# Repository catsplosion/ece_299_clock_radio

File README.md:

Development repo for the ECE 299 clock-radio project.

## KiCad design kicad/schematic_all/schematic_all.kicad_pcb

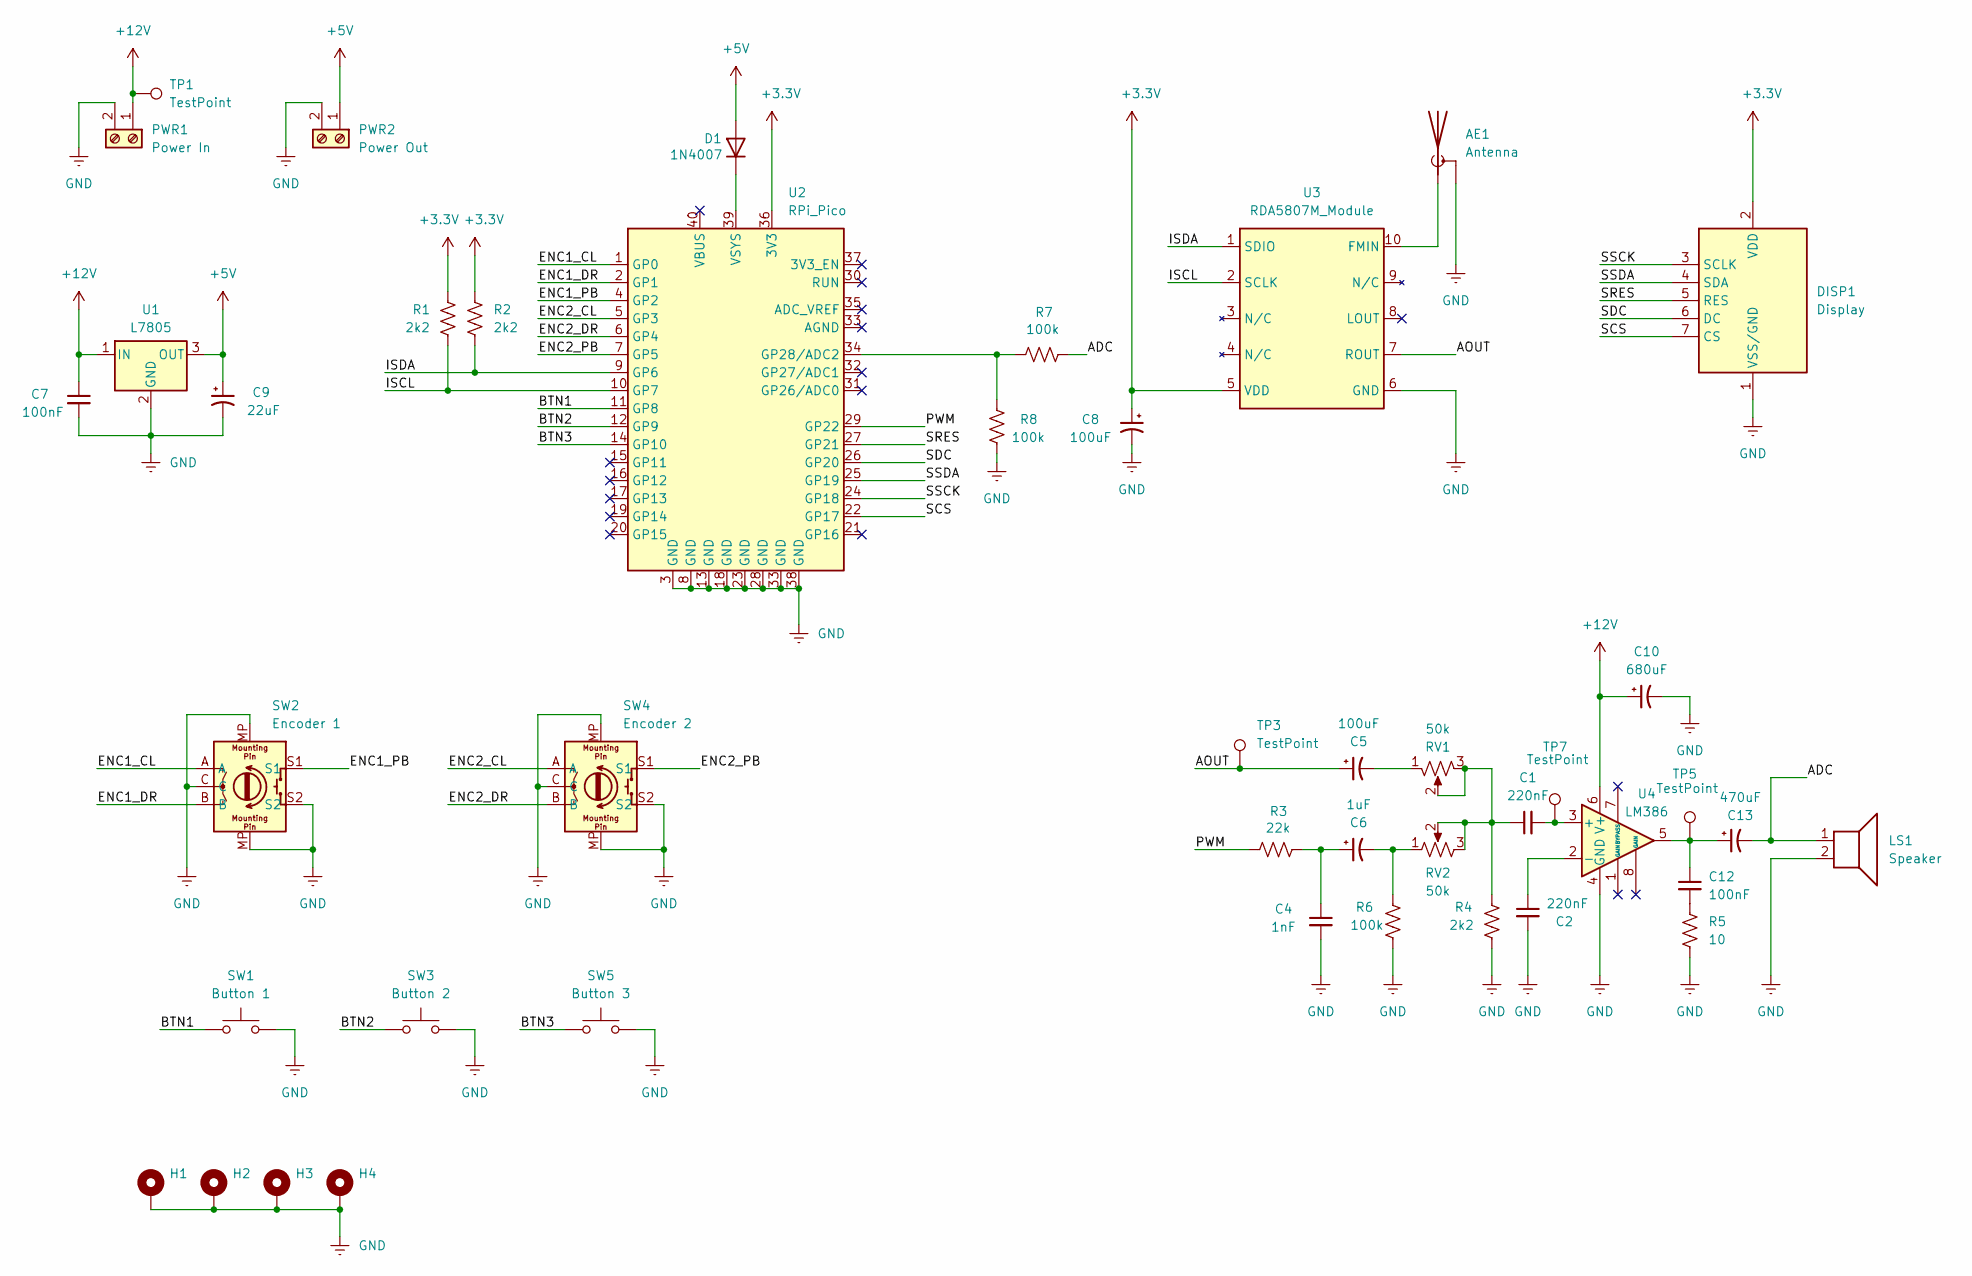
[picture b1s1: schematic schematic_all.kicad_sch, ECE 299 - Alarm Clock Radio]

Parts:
AE1: Antenna; TerminalBlock_Phoenix_MKDS-1,5-2_1x02_P5.00mm_Horizontal
C1, C2: 220nF; C_Disc_D5.0mm_W2.5mm_P5.00mm
C4: 1nF; C_Disc_D5.0mm_W2.5mm_P5.00mm
C5, C8: 100uF; CP_Radial_D5.0mm_P2.00mm
C6: 1uF; CP_Radial_D5.0mm_P2.00mm
C7, C12: 100nF; C_Disc_D3.0mm_W2.0mm_P2.50mm
C9: 22uF; CP_Radial_D5.0mm_P2.00mm
C10: 680uF; CP_Radial_D8.0mm_P3.50mm
C13: 470uF; CP_Radial_D8.0mm_P3.50mm
D1: 1N4007; D_DO-41_SOD81_P10.16mm_Horizontal
DISP1: Display; TerminalBlock_Phoenix_MKDS-1,5-7_1x07_P5.00mm_Horizontal
H1, H2, H3, H4: MountingHole_3.2mm_M3_Pad
LS1: Speaker; TerminalBlock_Phoenix_MKDS-1,5-2_1x02_P5.00mm_Horizontal
PWR1: Power In; TerminalBlock_Phoenix_MKDS-1,5-2_1x02_P5.00mm_Horizontal
PWR2: Power Out; PinHeader_1x02_P2.54mm_Vertical
R1, R2, R4: 2k2; R_Axial_DIN0207_L6.3mm_D2.5mm_P10.16mm_Horizontal
R3: 22k; R_Axial_DIN0207_L6.3mm_D2.5mm_P10.16mm_Horizontal
R5: 10; R_Axial_DIN0207_L6.3mm_D2.5mm_P10.16mm_Horizontal
R6, R7, R8: 100k; R_Axial_DIN0207_L6.3mm_D2.5mm_P10.16mm_Horizontal
RV1, RV2: 50k; Bourns_PTV09_Horiz
SW1: Button 1; TerminalBlock_Phoenix_MKDS-1,5-2_1x02_P5.00mm_Horizontal
SW2: Encoder 1; TerminalBlock_Phoenix_MKDS-1,5-4_1x04_P5.00mm_Horizontal
SW3: Button 2; TerminalBlock_Phoenix_MKDS-1,5-2_1x02_P5.00mm_Horizontal
SW4: Encoder 2; TerminalBlock_Phoenix_MKDS-1,5-4_1x04_P5.00mm_Horizontal
SW5: Button 3; TerminalBlock_Phoenix_MKDS-1,5-2_1x02_P5.00mm_Horizontal
TP1, TP3, TP5, TP7: TestPoint; PinHeader_1x01_P2.54mm_Vertical
U1: L7805; TO-220-3_Vertical
U2: RPi_Pico; RPi_Pico_TH
U3: RDA5807M_Module; RDA5807M_Module_TH
U4: LM386; DIP-8_W7.62mm_Socket

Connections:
+3.3V: C8.1, DISP1.2 (VDD), R1.1, R2.1, U2.36 (3V3), U3.5 (VDD)
+5V: C9.1, D1.2 (A), PWR2.1, U1.3 (OUT)
+12V: C7.1, C10.1, PWR1.1, TP1.1, U1.1 (IN), U4.6 (V+)
/ADC: C13.2, LS1.1, R7.2
/AOUT: C5.1, TP3.1, U3.7 (ROUT)
/BTN1: SW1.1, U2.11 (GP8)
/BTN2: SW3.1, U2.12 (GP9)
/BTN3: SW5.1, U2.14 (GP10)
/ENC1_CL: SW2.A, U2.1 (GP0)
/ENC1_DR: SW2.B, U2.2 (GP1)
/ENC1_PB: SW2.S1, U2.4 (GP2)
/ENC2_CL: SW4.A, U2.5 (GP3)
/ENC2_DR: SW4.B, U2.6 (GP4)
/ENC2_PB: SW4.S1, U2.7 (GP5)
/ISCL: R1.2, U2.10 (GP7), U3.2 (SCLK)
/ISDA: R2.2, U2.9 (GP6), U3.1 (SDIO)
/PWM: R3.2, U2.29 (GP22)
/SCS: DISP1.7 (CS), U2.22 (GP17)
/SDC: DISP1.6 (DC), U2.26 (GP20)
/SRES: DISP1.5 (RES), U2.27 (GP21)
/SSCK: DISP1.3 (SCLK), U2.24 (GP18)
/SSDA: DISP1.4 (SDA), U2.25 (GP19)
GND: AE1.2 (Shield), C2.2, C4.2, C7.2, C8.2, C9.2, C10.2, DISP1.1 (VSS/GND), H1.1, H2.1, H3.1, H4.1, LS1.2, PWR1.2, PWR2.2, R4.2, R5.2, R6.2, R8.1, RV1.4, RV1.5, RV2.4, RV2.5, SW1.2, SW2.C, SW2.MP, SW2.S2, SW3.2, SW4.C, SW4.MP, SW4.S2, SW5.2, U1.2 (GND), U2.3 (GND), U2.8 (GND), U2.13 (GND), U2.18 (GND), U2.23 (GND), U2.28 (GND), U2.33 (GND), U2.38 (GND), U3.6 (GND), U4.4 (GND)
unnamed: AE1.1 (A), U3.10 (FMIN)
unnamed: C1.1, R4.1, RV1.2, RV1.3, RV2.2, RV2.3
unnamed: C4.1, C6.1, R3.1
unnamed: C5.2, RV1.1
unnamed: C6.2, R6.1, RV2.1
unnamed: C12.1, C13.1, TP5.1, U4.5
unnamed: C12.2, R5.1
unnamed: D1.1 (K), U2.39 (VSYS)
unnamed: R7.1, R8.2, U2.34 (GP28/ADC2)
unnamed: C1.2, TP7.1, U4.3 (+)
unnamed: C2.1, U4.2 (-)

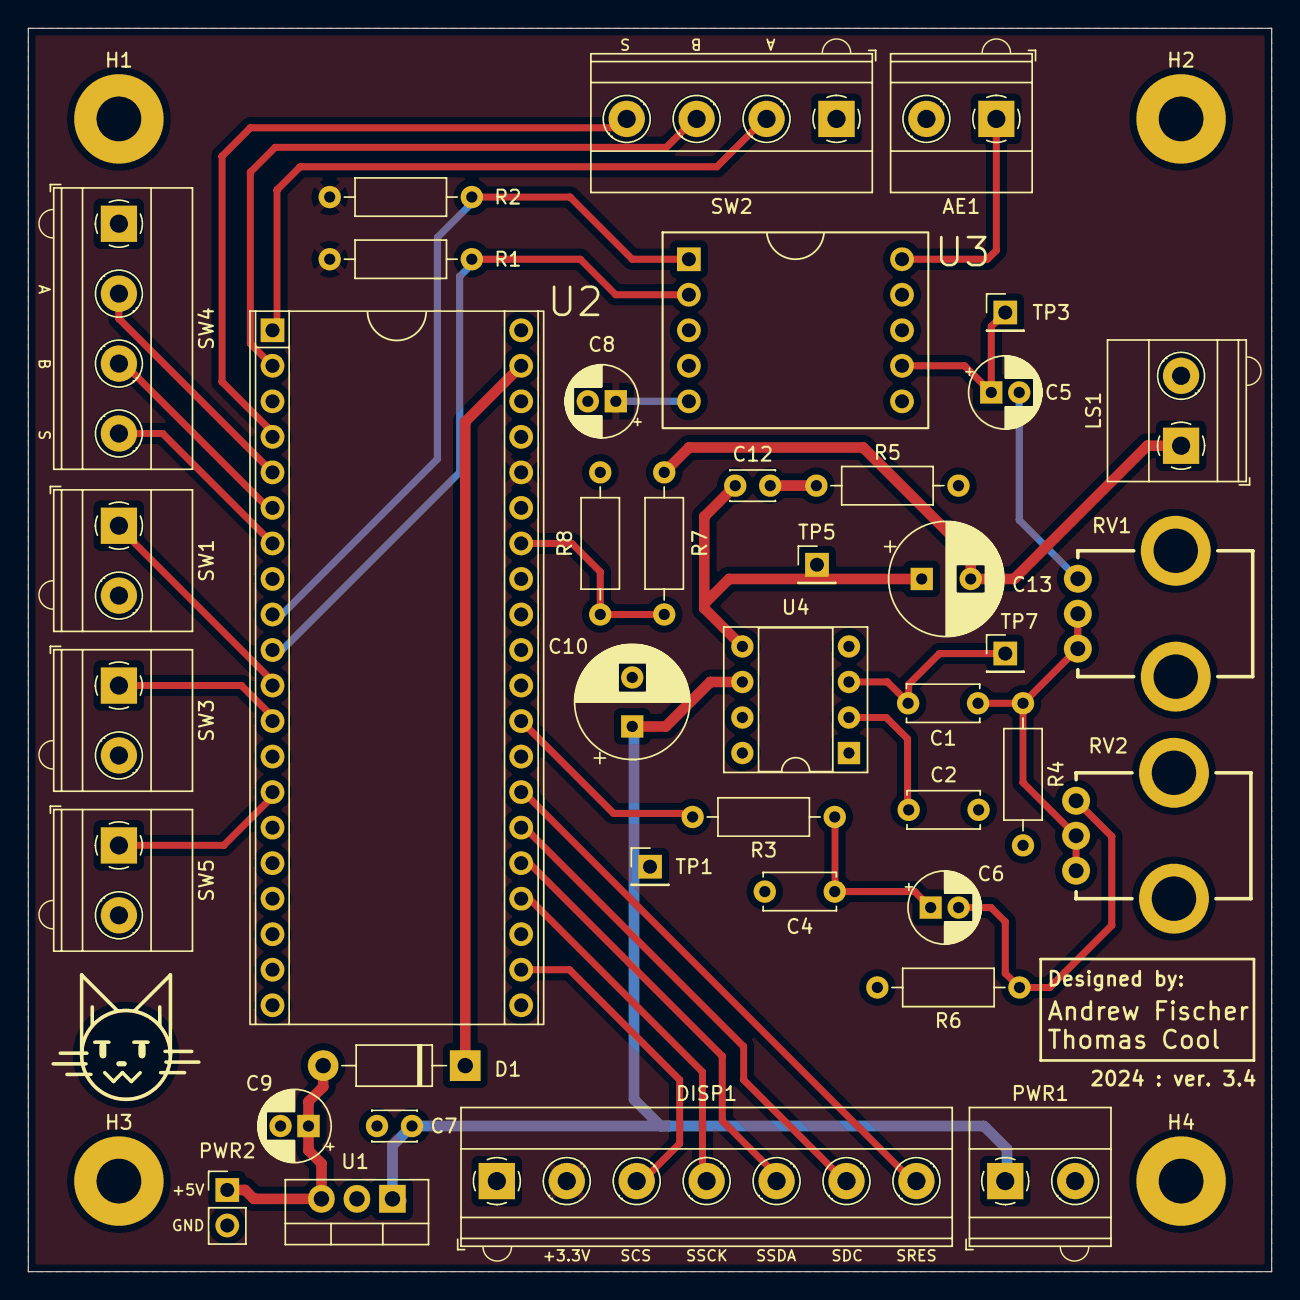
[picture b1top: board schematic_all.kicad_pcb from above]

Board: 2 copper layers, 88.9 x 88.9 mm, 44 parts (0 on the bottom side), 34 nets.

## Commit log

2024-06-30 add initial files
2024-07-01 add kicad project
2024-07-01 Version 0.1 of the menu system. Still some bugs to work out, rather barebones
2024-07-02 schematic v0.1
2024-07-02 schematic v0.2
2024-07-02 add rda5807 library
    from https://github.com/dawsonjon/101Things/tree/master/19_fm_radio
2024-07-02 fix bug with mono flag
2024-07-02 fix incorrect integer representation
2024-07-02 add mit license statement for rda5807 library
2024-07-03 Made some minor changes to the schmatic (Changed PWM pin, filtering capacitor footprints and values), and made some progress on the layout & design of the PCB
2024-07-03 Fixed small schematic save error
2024-07-03 Minor change to Power In placement, and added a corresponding track to VSYS
2024-07-03 Added files via upload
    Finished all traces and further organized hardware.
2024-07-03 move uploaded files to correct directory
2024-07-04 Added 12V supply + linear regulator to step-down to 5V
2024-07-04 Replaced jack with a terminal block
2024-07-04 fixes and cleanup of schematic
    added in extra capacitors for linear regulator
    cleaned up traces and aligned components
2024-07-04 flip SPI and power traces
2024-07-04 Minor changes
2024-07-04 Minor changes & Added additional testpoints
2024-07-05 adjustments on test points and ink
    move speaker test point to before capacitor
    increase size of designed by text
2024-07-05 fixes and silkscreen adjustment
    remove errant trace rectangle
    shift hidden silkscreen labels
2024-07-05 full board check
    replace incorrect radial cap with disc
    change capacitor values around amp
    add jack labels
    reground pot chassis
    tweak positions
2024-07-05 Fixed U3 Pad 5 3.3V connection
2024-07-05 Isolated C8 and U3 pin 5 track
2024-07-05 unpolarize amp coupling capacitors
2024-07-06 remove fill zone around U3 pin 5
2024-07-12 Complete overhaul to the logic of the menu system
2024-07-13 fix pico power issues
    swap regulator caps to match L4941 spec
    add +5V pinout
    add diode to prevent backfeeding from pico
2024-07-13 add trace and jumper between radio output and pico ADC
2024-07-13 replace ADC jumper with voltage divider
2024-07-13 move ADC from after C5 to after C13
2024-07-13 adjust ACD voltage divider ratio
2024-07-21 add clock state and boot modules
2024-07-22 Addded display class, and made minor changes & fixes to clockstate.py and boot.py
2024-07-22 fix push button inconsistency issue
    modify push button algorithm to use a cosistency check method
    remove delay parameter
2024-07-23 Bug fixes & features to boot.py, Menusystem.py, clockstate.py, display.py
2024-07-23 implement basic alarm and radio functionality
2024-07-23 integrate state functionality into menu system
2024-07-23 add toggle functionality to menu system
2024-07-23 cleanup: put render calls in menu handler rather than menu items
2024-07-23 cleanup and fix identical back methods
    move identical back functionality to superclass and fix bug when parent
    is unset
2024-07-23 add roller menu functionality for volume controls
    also fix bug with unbounded radio_volume attribute in state
    and fix bug with incorrect tuple conversion in set_alarm
2024-07-23 add snooze functionality on user input
    also fix incorrect 12hr clock string generation
    and fix bug with snooze times where alarm cannot be re-triggered between 55-60 seconds
2024-07-24 ADC & FFT Testing
2024-07-25 Version 1 of the ADC -> FFT code
2024-07-25 Slight modifications for testing
2024-07-25 minor bug fix
2024-07-25 add clock view and snooze features
    add clock view
    add led toggle menu item
    add snooze menu item
    fix bug when setting snooze delay
    add clock view reset timer
2024-07-26 Added New menu funcitonality forLEDS
2024-07-26 Added logic for leds
2024-07-26 Minor changes, still in progress
2024-07-27 Almost complete integration of ADC_Testing -> Leds_handler
2024-07-27 Unable to use multithreading
2024-07-28 wip LED handler cleanup
    separate sampling into own class
    cleanup main fft method
2024-07-29 add timezone offset to clockstate
2024-07-29 fix bug with rotary encoder hogging all the interrupts
2024-07-29 revamp menu structure and display
2024-07-29 add tall digits for clock view
2024-07-29 add temperature display
2024-07-29 use text month name
2024-07-29 Fixed LEDS, small additions and bug fixes
2024-07-30 FFT small fix
2024-07-30 QOL changes
2024-07-30 add more display features
    add time zone display
    add radio info display
    add alarm state display
2024-07-30 add clock time change menu item
2024-07-30 wip final fixes
2024-07-31 add in remaining features and fix PWM bugs
2024-08-02 various fixes for presentation
    move boot.py to main.py as boot.py file use was incorrect
    add icons for volume, mute, and signal strength
    add bad hack to get LED PWM to shut off
    add seek mode for radio frequency
    add display name for the various parameters
    offset volume diplay so it is 1-16
2024-08-05 reformat code and add comments
2024-08-05 add basic testing functionality
2024-08-06 add comments to testing code
